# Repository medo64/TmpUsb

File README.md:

# TmpUsb

TmpUsb is presented to a computer as an USB disk drive 11 KB in size (7-8 KB
usable). This drive can be then used to store any data (providing that size is
not the issue) but primary idea is to use it for the encryption keys. Once all
data has been copied to it, user would perform "arming" thus enabling
self-erase after approximately 3 seconds of being unplugged.

Basic use case for such behavior would be a BitLocker key storage. Having
encrypted server brings a lot of security benefits but with a cost of
re-entering keys on every restart. BitLocker can work around that by allowing
you to store keys on USB in order to decrypt content automatically.
Unfortunately this means that, if your server is stolen, you also give your
encryption key with it thus nullifying encryption.

By using TmpUsb your encryption keys will be deleted rendering data on stolen
server completely unusable. While this won't bring your server back, at least
data won't be readable any more.

## How It Works

When you plug TmpUsb in for the first time, it will start in "Not Armed" mode,
as visible from drive's label. Visually you would recognize this mode by the
fact that LED is on. At that time you can freely use it as you would any
standard USB drive. At this time you would copy your encryption keys to it and
change its label to "Arm" and unplug it.

On next plug-in (might be on another computer) LED will turn off and drive will
be considered armed. In this state drive will still behave as a standard USB
drive but only while it has power. If there is a power loss longer than
approximately three seconds (configurable, to allow for computer reset) drive
will self-erase and return to an empty state.

## LED

There is a single LED on a drive. If it is on, drive hasn't been armed and it
is safe to unplug it without going into risk of losing data to self-erase. Once
drive is armed, LED will turn off.

Upon self-erase, device will quickly blink three times. If self erasure was due
to validation error (i.e. drive content was corrupted) it will blink five
times.

## Commands

All commands are entered by changing drive label. Casing is not important.

### Arm

Gives command to TmpUsb to be "armed" on next plugin. This fits scenario where
user prepares encryption keys on one computer, arms TmpUsb and then plugs it in
on another computer. Only once TmpUsb has been plugged in for a second time, it
is considered armed and any further label changes won't change that status. In
this mode TmpUsb will tolerate short power loss (approximate three seconds) but
anything longer will trigger self-erase.

### ArmMax

As with Arm command, this will cause TmpUsb to be armed on next plugin.
However, unlike with Arm command, any power failure will trigger self-erasure
regardless of power-loss duration. On most computers this means that
self-erasure will be also triggered by a simple reset.

### Armed

Immediately "arms" TmpUsb without need to wait until next plugin. This is
useful in case where preparation of encryption keys is done on same computer
where those keys are to be used. It is just a shortcut that skips need for
unplug-plug that Arm command needs. Once armed, LED will be turned off and
status will remain armed even if drive label gets further changes.

### Calibrate

If standard power-loss buffer duration (approximately three seconds) is not
satisfactory, user can change drive label to `Calibrate` and unplug the drive.
Once drive is plugged back in, it will determine duration it was plugged out
for and use that as a new default. Notice that drive will be erased and its
label will say what is raw ADC value for given time. Do try to avoid values
less than 3. Due to nature of time keeping via the capacitor, values are really
rough and they are unusable beyond 10 seconds. Value determined by this
procedure will be used until either ArmMax or Reset are given. At that time
TmpUsb will revert to default three seconds.

### Reset

On next plug-in TmpUsb will perform self-erasure together with reset of all
settings.

## Security Risks

As expected, there are some security risks involved.

Major one is connected with fact that erasure of data, due to TmpUsb having no
battery, is possible only on next plug-in. If attacker is fast enough, he can
plug TmpUsb in another computer without triggering erasure. Mitigation strategy
for this attack is using `ArmMax` command in order to trigger erasure as soon
as power is lost.

Similarly, attacker can charge capacitor without actually turning TmpUsb on. On
next plug-in TmpUsb will think that less time passed than it actually has.
Mitigation strategy is also using `ArmMax` command.

Even using `ArmMax` you are not safe if attacker is technically savvy and has
access to TmpUsb that is currently working. It can put another power source in
parallel to USB and thus TmpUsb won't be aware at any time that the power was
lost.

Internal key storage is encrypted using the security feature of microcontroller
itself. In ideal world this would mean that, even if attacker has direct access
to chip, nobody would be able to read data without running it first. Of
course, this is intended to stop normal attackers only. Somebody with unlimited
resources (e.g. NSA) will not be deterred by this.

Regardless of these attacks, TmpUsb will probably protect you from 99.9%
attackers, especially if they are not aware its presence. It is not be-all and
end-all device but it surely beats keeping keys on a normal USB drive.

## Known Issues

Device has no battery, time is kept only by monitoring voltage decay on a big
capacitor. Major downfall is the fact that such timing is imprecise and doesn't
allow for a big time spans. In practice TmpUsb can deal with up to 10 seconds
of delay.

Since most operating systems cannot really format such a small drive and such
attempt might possibly damage logical structure, decision has been made to
check MBR and boot sector (including partition table) areas on every boot.
Effect of this verification is that any change to verified areas is not
possible and drive will self-erase if such change is noted.

Chip used for TmpUsb has flash specified for at least 10000 write cycles. Since
there is no block remapping as it is custom on the modern flash drives, this
roughly means that you can safely write to this drive approximately 5000 times
(it does suffer from high write amplification). While it will probably handle a
bit more, this is definitely not the device when constant writing is expected.

Total size of this drive is 11 KB. However, this is not a size user will have
available. Six sectors (3 KB) are immediately taken by mandatory MBR and boot
sector, followed by FAT and a root directory entries. OS only gets to see 8 KB.
Once drive is plugged-in, some Windows versions will add its System Volume
Information folder on each drive it sees and that means that it gets hit with
additional 1 KB penalty and at least four directory entries are gone. Under
Windows available size is thus 7-8 KB (depending on version) while we get 8 KB
under Linux.

---

*You can check my blog and other projects at [www.medo64.com](https://www.medo64.com/).*

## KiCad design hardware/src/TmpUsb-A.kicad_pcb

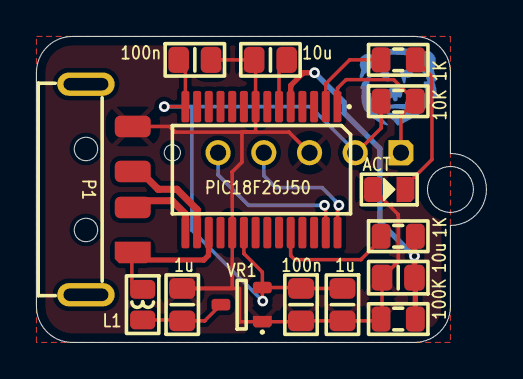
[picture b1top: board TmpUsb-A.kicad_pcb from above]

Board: 2 copper layers, 25.0 x 17.0 mm, 16 parts (1 on the bottom side), 12 nets.

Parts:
C1, C2: 100n; C (0805)
C3, C4: 1u; C (0805)
C5, C6: 10u; C (0805)
DS1: ACT; DS (0805)
L1: 40R; L Ferrite (0805)
P1: 48037-2200; P USB A 2.0 (4w)
R1, R2: 1K; R (0805)
R3: 10K; R (0805)
R4: 100K; R (0805)
U1: PIC18F26J50; U Micro PIC18F26J50 (SSOP-28)
VR1: MCP1700; VR Linear MCP1700 (SOT23-3)
Z?: Medo64; ICON Medo64

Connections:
+3.3V: C1.1, C2.1, C4.1, R3.1, U1.14, U1.20, VR1.2
+5V: C3.1, L1.2, VR1.3
CAP: C6.1, R2.2, R4.1, U1.5
CAP_POWER: R2.1, U1.24
GND: C1.2, C2.2, C3.2, C4.2, C5.2, C6.2, DS1.2, P1.4, R4.2, U1.8, U1.19, VR1.1
ICSP_VPP: R3.2, U1.1
LED: R1.1, U1.2
LED': DS1.1, R1.2
USB_D+: P1.3, U1.16
USB_D-: P1.2, U1.15
VCAP: C5.1, U1.6
VCC: L1.1, P1.1, U1.17

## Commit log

2013-08-11 Initial commit.
2013-08-12 Added MCLR circuit.
2013-09-16 Added battery.
2013-11-20 Refactoring.
2013-11-20 Added additional decoupling capacitor.
2013-11-26 Added CR2032 battery and a major refactoring.
2013-11-27 Updated ordering numbers.
2014-03-16 Added tag A1348 for changeset cefe2dbc5a4c
2014-03-16 Added tag A1403 for changeset e9e3ad5ab537
2014-03-16 First working firmware.
2014-03-16 Moved tag A1348 to changeset 3b5285a0ec03 (from changeset cefe2dbc5a4c)
2014-03-16 Added tag A1332 for changeset cefe2dbc5a4c
2014-03-16 Moved tag A1332 to changeset f28ac22f9bb6 (from changeset cefe2dbc5a4c)
2014-03-17 Customizing Microchip's USB responses.
2014-03-17 Refactoring USB code.
2014-03-17 Changed to large memory model to avoid type qualifier mismatch warning.
2014-03-17 Hex file is copied to Binaries folder.
2014-03-17 Basic erase code.
2014-03-18 Minimalistic design refactoring.
2014-03-19 Added tag A1411 for changeset dbe4e969d3f5
2014-03-30 Just a standard LED.
2014-03-30 Added timing.
2014-03-31 Checking validity on startup.
2014-04-05 Refactoring and adding calibration label.
2014-04-05 Added settings.
2014-04-05 All components on top side.
2014-04-05 A bit thinner (23x17).
2014-04-05 Charging resistor is 1K.
2014-04-06 Added 100K bleed-off resistor (to get more consistent values).
2014-04-06 Adjusting default value for 100K bleed-off.
2014-04-06 Detecting Arming while plugged in.
2014-04-06 Refactoring label reading functions.
2014-04-06 Using BOOL for booleans.
2014-04-06 Adding Reset and Arm commands + some refactoring.
2014-04-06 D+ and D- are about the same length now.
2014-04-06 Added tag A1414 for changeset 6f0cc64a3a53
2014-04-06 Skipping dirty flag when checking disk validity.
2014-04-08 Fixed accidental clear.
2014-04-08 Disk reset after 3 seconds.
2014-04-08 Refactoring LED position.
2014-04-09 Blinking 5 times on validation failure.
2014-04-09 Added ArmMax command.
2014-04-09 Increasing startup charge.
2014-04-09 Fixing LED name.
2014-04-09 Erasing drive if 5V goes missing.
2014-04-10 Initial working XC8 version (no TmpUsb-specific functionality). Based on Microchip Libraries for Applications [2013-12-20]
2014-04-10 Initial working XC8 with TmpUsb specific code.
2014-04-10 Clean-up of default sectors.
2014-04-10 Drive is exactly 8 KB.
2014-04-10 Changed USB descriptors.
2014-04-11 Added flash size check.
2014-04-11 Increased root directory entries count to 32.
2014-04-11 Fixed accidental allocation of first data sector.
2014-04-11 Fixed wrong root entries allocation in Microchip's code.
2014-04-13 Using Microchip-assigned Product ID.
2014-04-13 Changing INQUIRY response.
2014-04-13 Added script to automatically randomize serial number string descriptor.
2014-04-13 Changing USB descriptor.
2014-04-14 Added USB power test points.
2014-04-15 Backed out changeset: e115b8e5b695
2014-04-22 Added tag A1415 for changeset 396d464dabe9
2014-04-28 Changing txt a bit.
2014-04-30 Changing capacitor type.
2014-05-04 Adding readonly command.
2014-05-05 Heat-shrink length is adjusted.
2014-05-05 Updated product revision.
2014-05-06 Added LED blink on write.
2014-05-06 Removing LED on/off.
2014-05-06 Refactoring a bit.
2014-05-06 ArmMax reset will restore timing charge.
2014-05-07 Increased sector count to be compatible with Windows 7.
2014-05-07 Increasing size a bit more.
2014-05-12 ReadOnly arms device on next restart.
2014-05-12 Refactoring init a bit.
2014-05-12 Forcing rebuild on every programming.
2014-06-04 Added forgetful.
2014-06-15 Updated silk screen.
2014-10-31 Added VID/PID.
2014-12-26 Added read-me.
2014-12-26 Fixed read-me.
2015-04-27 Adjusted for Git.
2015-04-28 Added picture.
2015-05-03 Adjusted readme.
2015-09-04 Added lanyard hole.
2015-09-22 Bigger chain hole.
2015-10-05 Keychain hole is a bit bigger.
2015-10-24 Changed USB part number.
2015-10-30 Expanded ring hole.
2016-04-17 Removed lanyard hole.
2016-04-17 Adjusted for MPLAB X 3.26 and XC8 1.37.
2016-05-07 Re-added lanyard hole.
2017-05-28 Changed bear icon.
2017-06-03 Adjusted icon.
2018-07-08 Adjusted DigiKey IDs.
2018-07-08 Adjusted to work with XC8 1.45.
2018-09-03 Updated for MPLAB X IDE 5.0 and XC8 1.45.
2019-05-08 Removed incorrect ICSP 3D model
2019-08-25 Added variant using 2x5 header
2021-02-02 Moved file around
2021-02-02 First USB 3 header setup
2021-02-02 Updated USB header connector
2021-02-03 Refactoring wires a bit
2021-02-12 Adjusted layers a bit
2021-02-12 Minor copper pour refactorings
2021-02-17 Updated ferrite part size
2021-02-18 Refactoring directories and files
2021-02-18 Updated default serial number
2021-02-20 Refactored to make smaller board with USB on side
2021-02-20 Shaved off a bit more
2021-02-20 Refactoring silkscreen and copper pours
2021-02-21 Making 2.0 header smaller by removing USB connector
2021-02-21 Refactoring a bit
2021-02-22 Refactoring copper pours
2021-02-22 Fixed USB 3.0 header connector pinout
2021-02-23 H2 has edge connector now
2021-02-23 H2 board is smaller a bit
2021-02-23 Refactoring vias a bit
2021-02-23 Updating USB3 motherboard header connector
2021-02-24 Fixed USB3 header connector orientation
2021-03-08 Refactored TmpUsb-H3 to make it smaller
2021-03-08 Refactoring traces a bit
2021-03-20 Added suggested soldering order
2021-03-21 Refactored H3 to have TmpUsb assigned to USB1 (due to A1SRi)
2021-03-22 Refactored to use vertical connector
2021-03-22 Updated header
2021-03-22 Refactoring
2021-03-22 Added type-A copper pour
2021-03-24 Added trace colors
2021-03-25 Refactored layer stackup
2021-03-25 Refactoring layer stackup
2021-03-26 Refactoring USB traces to improve impedance
2021-03-26 Cleaning up silkscreen
2022-03-05 Added variant allowing for 5VSB line
2022-03-05 Minor refactoring
2022-03-19 Removed solder mask from 5Vstby line
2022-03-19 Moved 5Vstby pad a bit
2023-07-09 Added KiCad PCB
2023-07-09 Fixed USB connector DRC checks
2023-07-09 Cleaning up traces and adding copper pour
2023-07-09 Renamed project files and some minor updates
2023-07-09 Added make script for gerber output
2023-07-09 Replaced ferrite bead footprint
2023-07-09 Updated footprint a bit
2023-07-09 Added schematics
2023-07-09 Renamed project a bit
2023-07-10 Updated make script to adjust text on PCB
2023-07-10 Updating footprints and net names
2023-07-10 Adding a few colors to nets
2023-07-11 Moved diode to center
2023-07-11 Fixed make script
2023-07-11 Pogo ICSP has copper exposed only on one side
2023-07-11 Added case models
2023-07-19 Updated ferrite silkscreen
2023-07-21 Moving PIC silk-screen
2023-08-27 Cleaning up the board and updated footprints
2023-08-27 Removed make file
2023-08-27 Updated ICSP footprint
2023-08-27 Updated kicad PCB name
2023-08-29 Using 5-pin ICSP pogo connector
2023-08-29 Updated via size
2023-08-30 Updated pogo footprint
2023-09-03 Updated silkscreen sizes
2023-09-03 Updated footprints a bit
2023-09-04 Updated footprints
2023-10-08 First attempt to update for new XC8
2023-10-08 Updated USB files to Microchip MLA v2018_11_26
2023-10-08 Fixed script to randomize serial
2023-10-09 Rotated LED around and minor component updates
2023-10-09 Rolling back MLA v2018_11_26 update
2023-10-09 Moving silkscreen around
2023-10-09 Reorganizing traces a bit
2023-10-09 First go at MB header USB
2023-10-09 Updating descriptors a bit
2023-10-25 Updated pogo connector
2024-05-18 Removed extra project files
2024-05-18 Updating footprints
2024-05-18 Updated WOL connectort to AMP CT
2024-05-18 Fixing connector designators
2024-05-18 Added case for H2 variant
2024-05-19 Adjusting silkscreen a bit
2024-05-19 Renamed V+ nets
2024-05-19 Swapping diodes around
2024-07-28 Adjusted silkscreen
2024-07-28 Updated H2 case
2024-07-28 Moved case to a separate directory
